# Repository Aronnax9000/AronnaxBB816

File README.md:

# AronnaxBB816
Memory Board
16777216 bytes = 16 MB = 0x1000000
65536 bytes = 64 KB 0x10000 (0x0000 - 0xFFFF)
There are sixteen 64 KB banks in a megabyte.
2^20 1 megabyte 0x100000 

0x000000-0x07FFFF Low  512 KB RAM
0x080000-0x0FFFFF High 512 KB RAM
0x000100-0x0001FF Bank 0 Page 1 I/O
                  VIA 0 (16 bytes)
                  VIA 1 (16 bytes)
                  ACIA (4 bytes)
                  
0x008000-0x00FFFF EEPROM (read when E signal is active)
                  RAM (write always on ~WR, read when E signal is not active)

Board uses A0-A19 (20 lines). 

Active when MEG0 = ~A23 * ~A22 * ~A21 * ~A20.
MEG0_UPPER = MEG0 * A19
MEG0_LOWER = MEG0 * ~A19

~BANK0_UPPER = ~BANK0 + ~A15
~BANK0_LOWER = ~BANK0 + A15

~EEPROM_CS = ~E + ~BANK0_UPPER

I/O Active when BANK0_LOWER * A8 * ~A9 * ~A10 * ~A11 * ~A12 * ~A13 * ~A14

Vector Pull Rewrite

2.28 Vector Pull (VPB)

The Vector Pull active low output indicates that a vector location is being addressed during an interrupt
sequence. VPB is low during the last two interrupt sequence cycles, during which time the processor loads
the PC with the interrupt handler vector location. The VPB signal may be used to select and prioritize
interrupts from several sources by modifying the vector addresses.

Table 5-2 Emulation Mode Vector Locations (8-bit Mode)

|Address | Label | Function | 
00FFFE,F | IRQB/BRK | Hardware/Software | 
00FFFC,D | RESETB | Hardware | 
00FFFA,B | NMIB | Hardware | 
00FFF8,9 | ABORTB | | Hardware | 
00FFF6,7 | (Reserved) | Hardware | 
00FFF4,5 | COP | Software | 
00FFF2,3 | (Reserved) | 
00FFF0,1 | (Reserved) | 

Table 5-3 Native Mode Vector Locations (16-bit Mode)

Address | Label | Function | 
00FFEE,F | IRQB | Hardware | 
00FFEC,D | (Reserved) | 
00FFEA,B | NMIB | Hardware | 
00FFE8,9 | ABORTB| | 
00FFE6,7 | BRK | Software | 
00FFE4,5 | COP | Software| 
00FFE2,3 | (Reserved) | |
00FFE0,1 | (Reserved) | |

The VP output is low during the two cycles used for vector location access. When an interrupt is executed,
D=0 and I=1 in Status Register P.

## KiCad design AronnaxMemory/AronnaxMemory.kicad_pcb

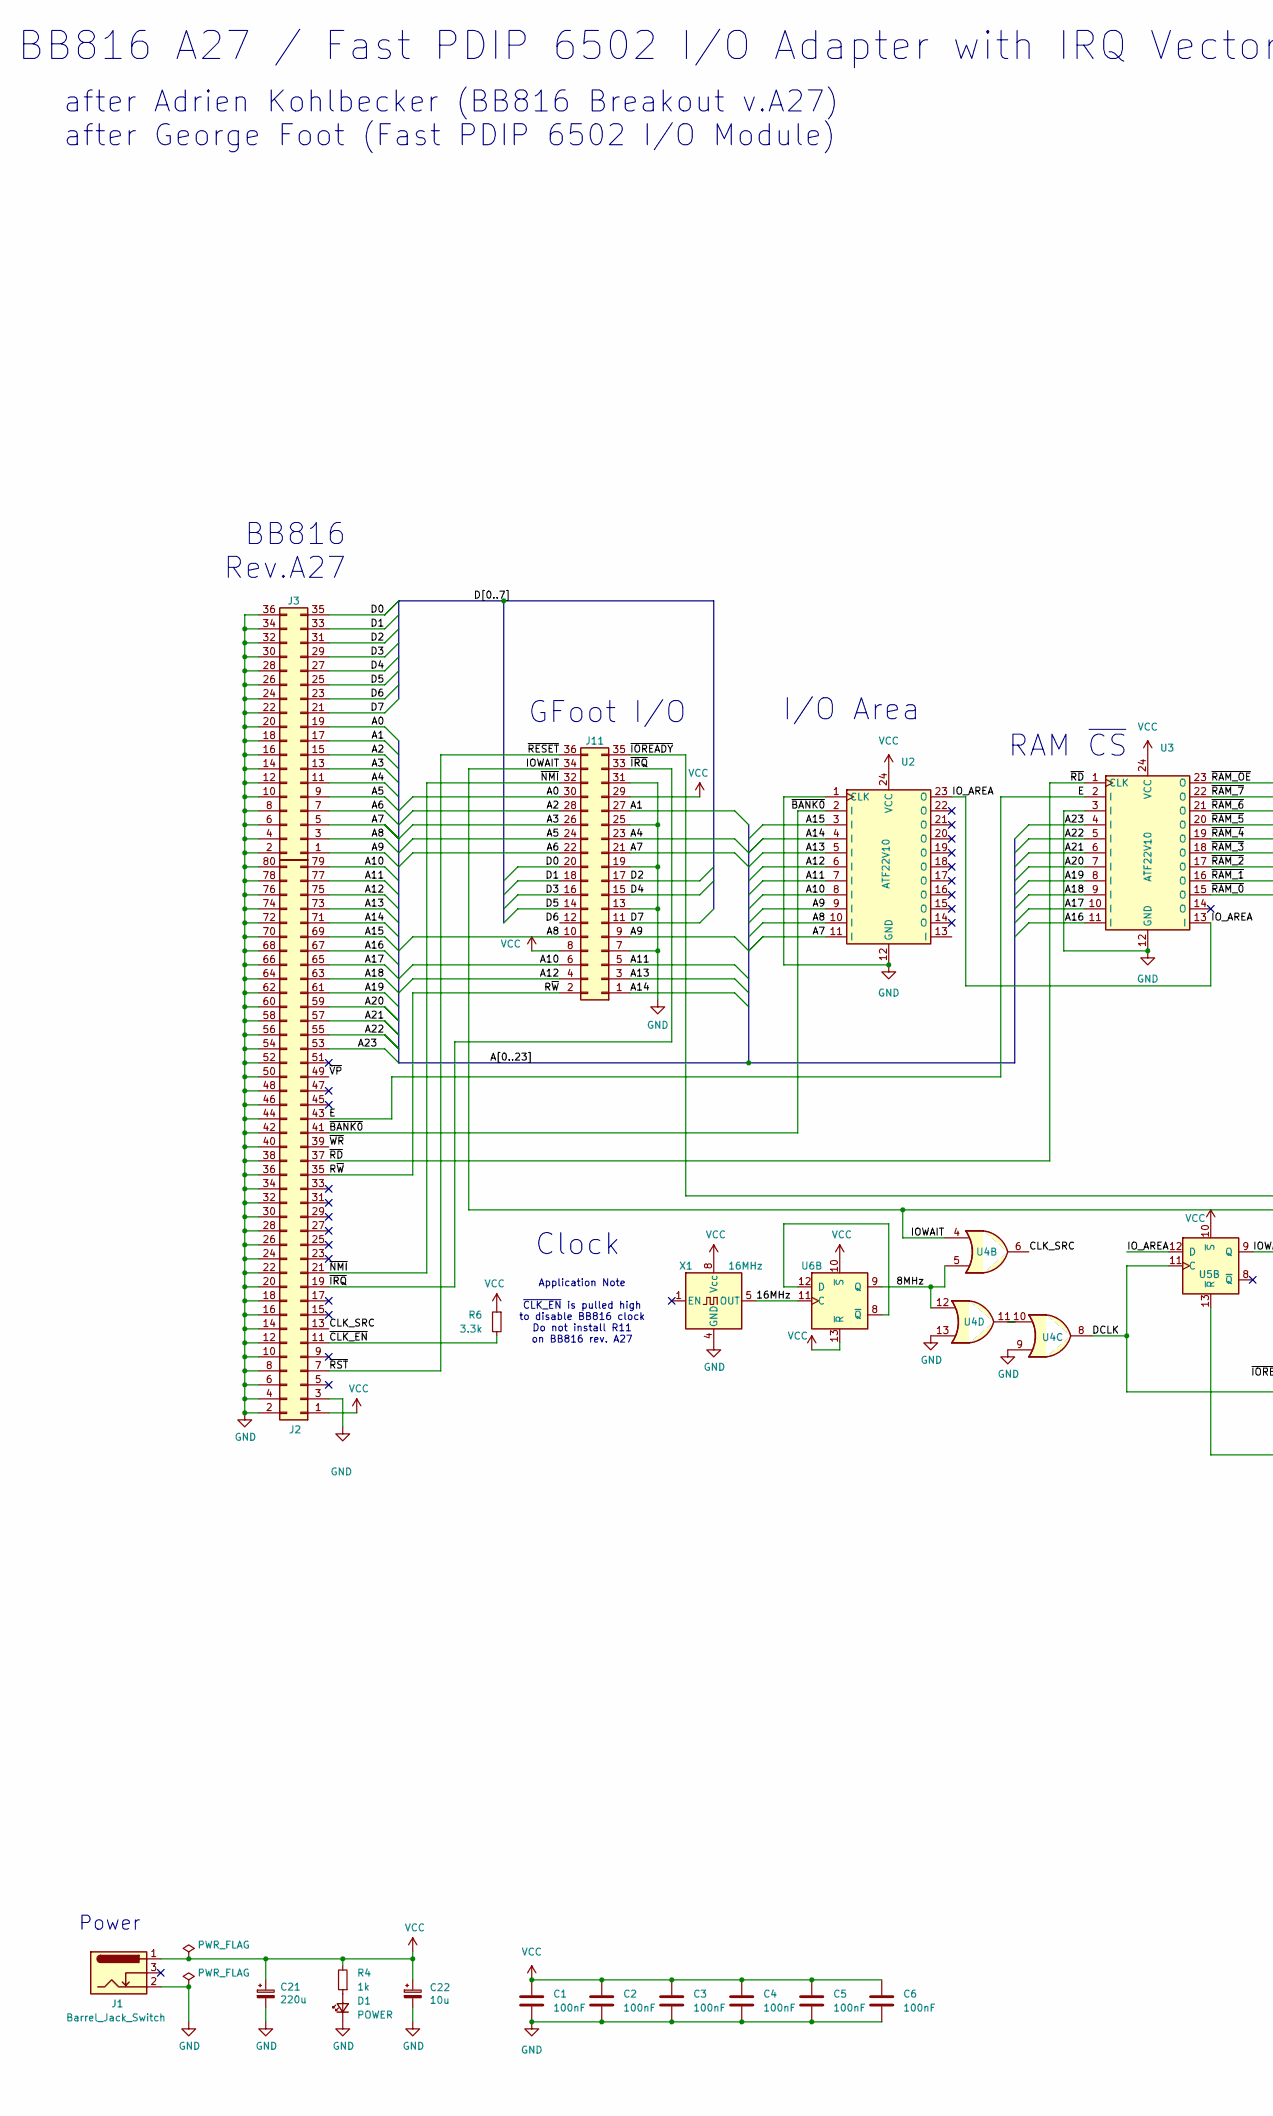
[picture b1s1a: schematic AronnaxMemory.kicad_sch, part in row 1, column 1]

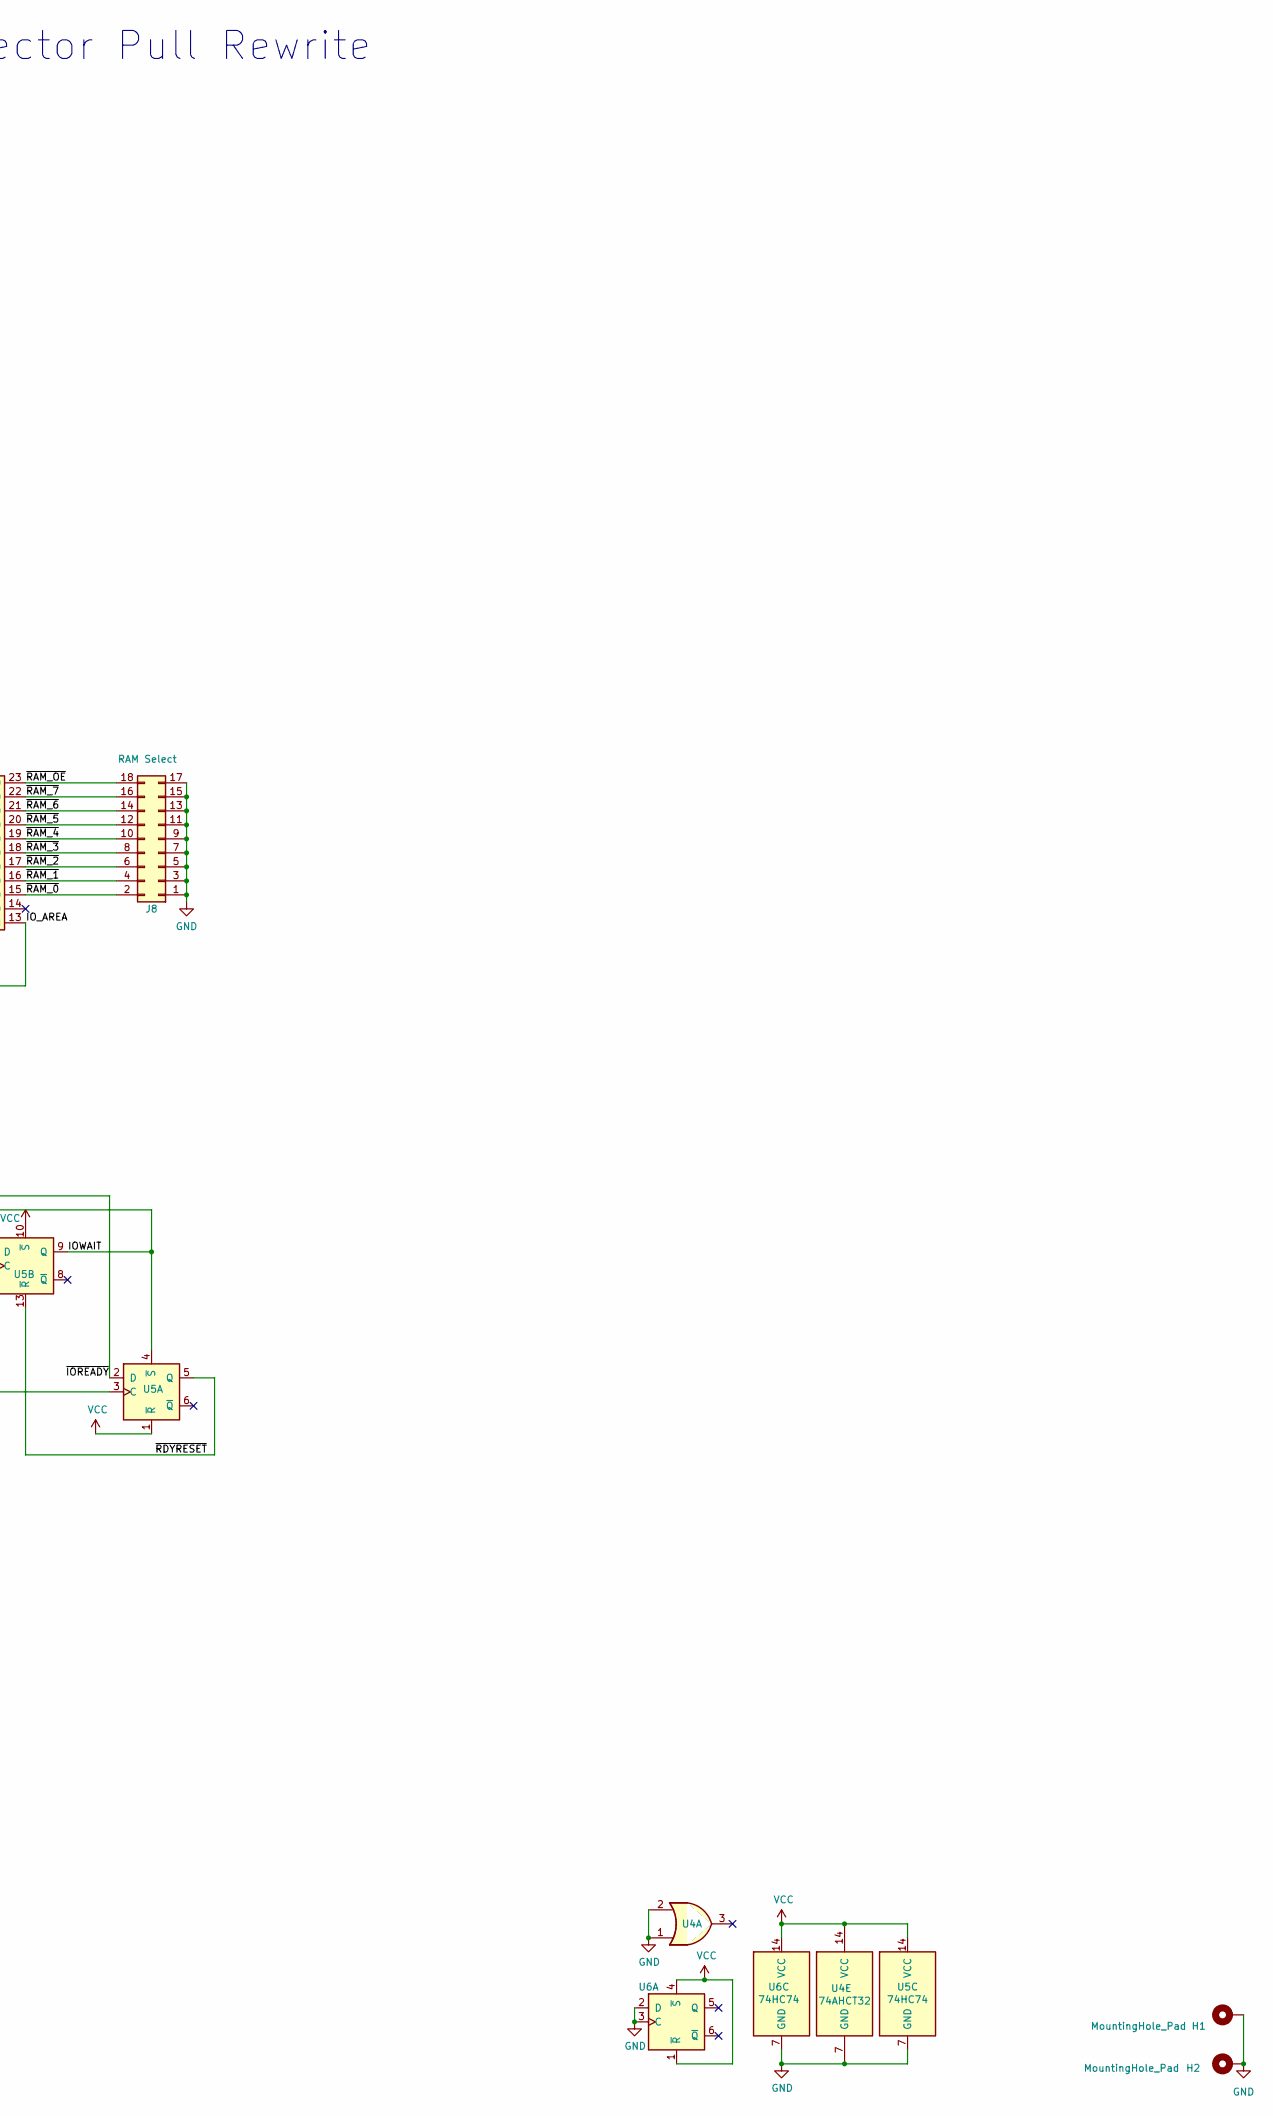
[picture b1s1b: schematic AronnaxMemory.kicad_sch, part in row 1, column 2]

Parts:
C1, C2, C3, C4, C5, C6: 100nF; C_Disc_D3.4mm_W2.1mm_P2.50mm
C21: 220u; CP_Radial_D6.3mm_P2.50mm
C22: 10u; CP_Radial_D4.0mm_P1.50mm
D1: POWER; LED_D3.0mm
H1, H2: MountingHole_Pad; MountingHole_3.2mm_M3_Pad
J1: Barrel_Jack_Switch; BarrelJack_Horizontal
J2: Conn_02x40_Odd_Even; PinHeader_2x40_P2.54mm_Vertical
J3: Conn_02x18_Odd_Even; PinHeader_2x18_P2.54mm_Vertical
J8: RAM Select; PinHeader_2x09_P2.54mm_Vertical
J11: Conn_02x18_Odd_Even; PCB_Edge_36pin
R4: 1k; R_Axial_DIN0207_L6.3mm_D2.5mm_P7.62mm_Horizontal
R6: 3.3k; R_Axial_DIN0207_L6.3mm_D2.5mm_P7.62mm_Horizontal
U2, U3: ATF22V10; DIP-24_W7.62mm_Socket
U4: 74AHCT32; DIP-14_W7.62mm_Socket
U5, U6: 74HC74; DIP-14_W7.62mm_Socket
X1: 16MHz; Oscillator_DIP-8

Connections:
/8MHz: U4.5, U4.12, U6.9 (Q)
/16MHz: U6.11 (C), X1.5 (OUT)
/A0: J3.19, J11.30
/A1: J3.17, J11.27
/A2: J3.15, J11.28
/A3: J3.13, J11.26
/A4: J3.11, J11.23
/A5: J3.9, J11.24
/A6: J3.7, J11.22
/A7: J3.5, J11.21, U2.11 (I)
/A8: J3.3, J11.10, U2.10 (I)
/A9: J3.1, J11.9, U2.9 (I)
/A10: J2.79, J11.6, U2.8 (I)
/A11: J2.77, J11.5, U2.7 (I)
/A12: J2.75, J11.4, U2.6 (I)
/A13: J2.73, J11.3, U2.5 (I)
/A14: J2.71, J11.1, U2.4 (I)
/A15: J2.69, U2.3 (I)
/A16: J2.67, U3.11 (I)
/A17: J2.65, U3.10 (I)
/A18: J2.63, U3.9 (I)
/A19: J2.61, U3.8 (I)
/A20: J2.59, U3.7 (I)
/A21: J2.57, U3.6 (I)
/A22: J2.55, U3.5 (I)
/A23: J2.53, U3.4 (I)
/CLK_SRC: J2.13, U4.6
/D0: J3.35, J11.20
/D1: J3.33, J11.18
/D2: J3.31, J11.17
/D3: J3.29, J11.16
/D4: J3.27, J11.15
/D5: J3.25, J11.14
/D6: J3.23, J11.12
/D7: J3.21, J11.11
/DCLK: U4.8, U5.3 (C), U5.11 (C)
/E: J2.43, U3.2 (I)
/IOWAIT: J11.34, U4.4, U5.4 (~S), U5.9 (Q)
/IO_AREA: U2.23 (O), U3.13 (I), U5.12 (D)
/R~W: J2.35, J11.2
/~BANK0: J2.41, U2.2 (I)
/~CLK_EN: J2.11, R6.2
/~IOREADY: J11.35, U5.2 (D)
/~IRQ: J2.19, J11.33
/~NMI: J2.21, J11.32
/~RAM_0: J8.2, U3.15 (O)
/~RAM_1: J8.4, U3.16 (O)
/~RAM_2: J8.6, U3.17 (O)
/~RAM_3: J8.8, U3.18 (O)
/~RAM_4: J8.10, U3.19 (O)
/~RAM_5: J8.12, U3.20 (O)
/~RAM_6: J8.14, U3.21 (O)
/~RAM_7: J8.16, U3.22 (O)
/~RAM_OE: J8.18, U3.23 (O)
/~RDYRESET: U5.5 (Q), U5.13 (~R)
/~RD: J2.37, U3.1 (CLK)
/~RESET: J2.7, J11.36
/~VP: J2.49
/~WR: J2.39
GND: C1.2, C2.2, C3.2, C4.2, C5.2, C6.2, C21.2, C22.2, D1.1 (K), H1.1, H2.1, J1.2, J2.2, J2.3, J2.4, J2.6, J2.8, J2.10, J2.12, J2.14, J2.16, J2.18, J2.20, J2.22, J2.24, J2.26, J2.28, J2.30, J2.32, J2.34, J2.36, J2.38, J2.40, J2.42, J2.44, J2.46, J2.48, J2.50, J2.52, J2.54, J2.56, J2.58, J2.60, J2.62, J2.64, J2.66, J2.68, J2.70, J2.72, J2.74, J2.76, J2.78, J2.80, J3.2, J3.4, J3.6, J3.8, J3.10, J3.12, J3.14, J3.16, J3.18, J3.20, J3.22, J3.24, J3.26, J3.28, J3.30, J3.32, J3.34, J3.36, J8.1, J8.3, J8.5, J8.7, J8.9, J8.11, J8.13, J8.15, J8.17, J11.7, J11.13, J11.19, J11.25, J11.31, U2.1 (CLK), U2.12 (GND), U3.3 (I), U3.12 (GND), U4.1, U4.2, U4.7 (GND), U4.9, U4.13, U5.7 (GND)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
unnamed: D1.2 (A), R4.1
unnamed: U4.10, U4.11
unnamed: U6.8 (~Q), U6.12 (D)
VCC: C1.1, C2.1, C3.1, C4.1, C5.1, C6.1, C21.1, C22.1, J1.1, J2.1, J11.8, J11.29, R4.2, R6.1, U2.24 (VCC), U3.24 (VCC), U4.14 (VCC), U5.1 (~R), U5.10 (~S), U5.14 (VCC), U6.1 (~R), U6.4 (~S), U6.10 (~S), U6.13 (~R), U6.14 (VCC), X1.8 (Vcc)

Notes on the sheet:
RAM ~{CS}
Power
GFoot I/O
BB816 Rev.A27
after Adrien Kohlbecker (BB816 Breakout v.A27) after George Foot (Fast PDIP 6502 I/O Module)
Clock
I/O Area
BB816 A27 / Fast PDIP 6502 I/O Adapter with IRQ Vector Pull Rewrite
Application Note ~{CLK_EN} is pulled high to disable BB816 clock Do not install R11 on BB816 rev. A27

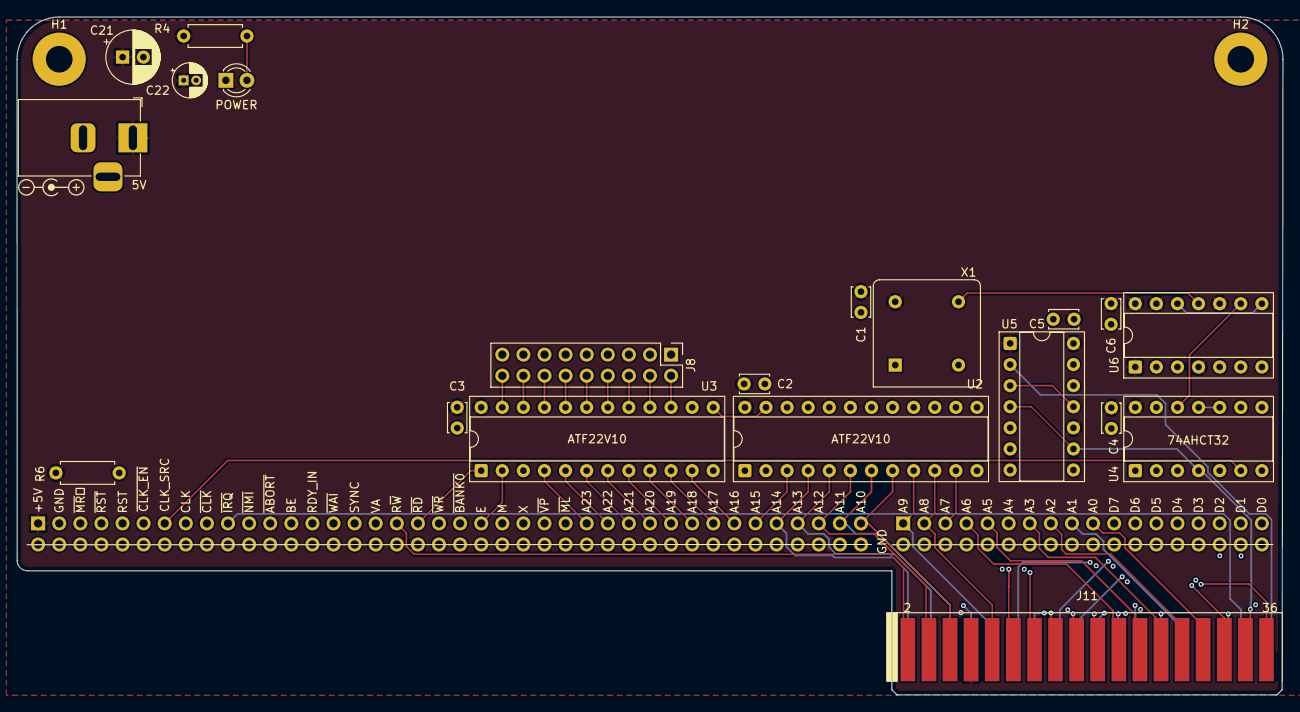
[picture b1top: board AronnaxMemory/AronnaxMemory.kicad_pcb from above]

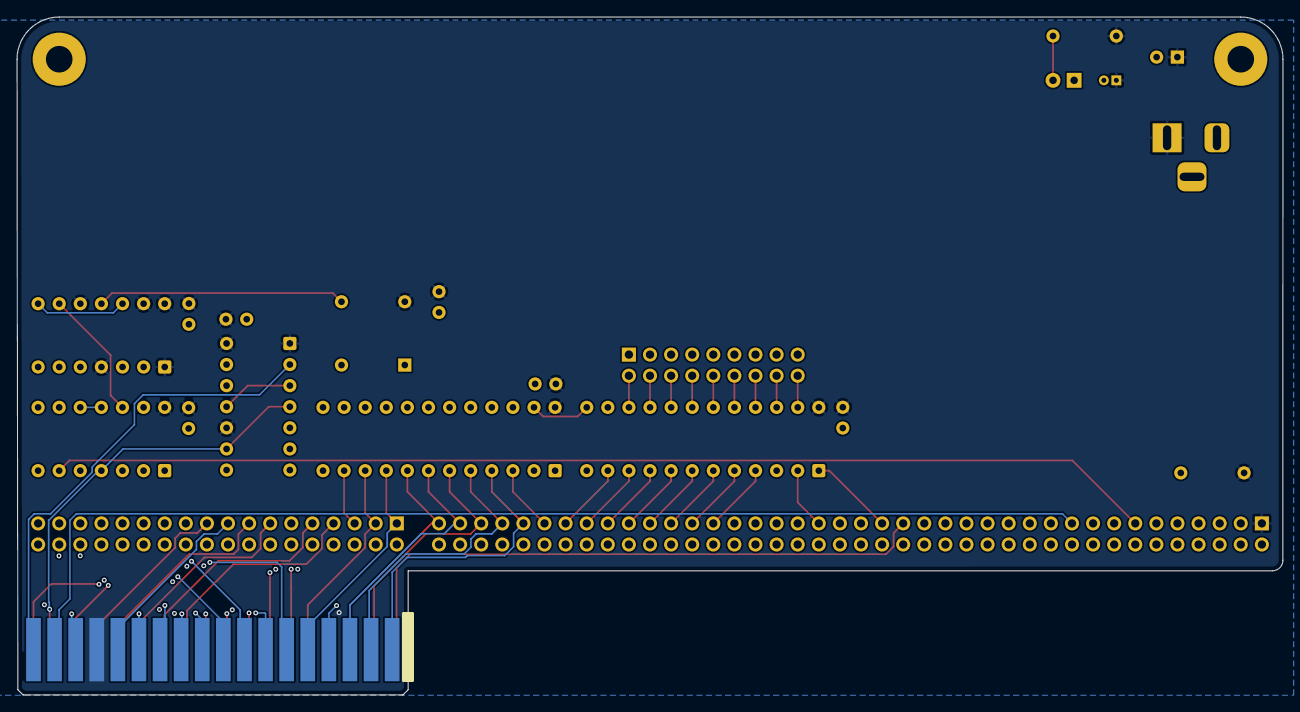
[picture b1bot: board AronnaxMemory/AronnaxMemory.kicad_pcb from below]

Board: 6 copper layers, 152.4 x 81.6 mm, 24 parts (2 on the bottom side), 62 nets.

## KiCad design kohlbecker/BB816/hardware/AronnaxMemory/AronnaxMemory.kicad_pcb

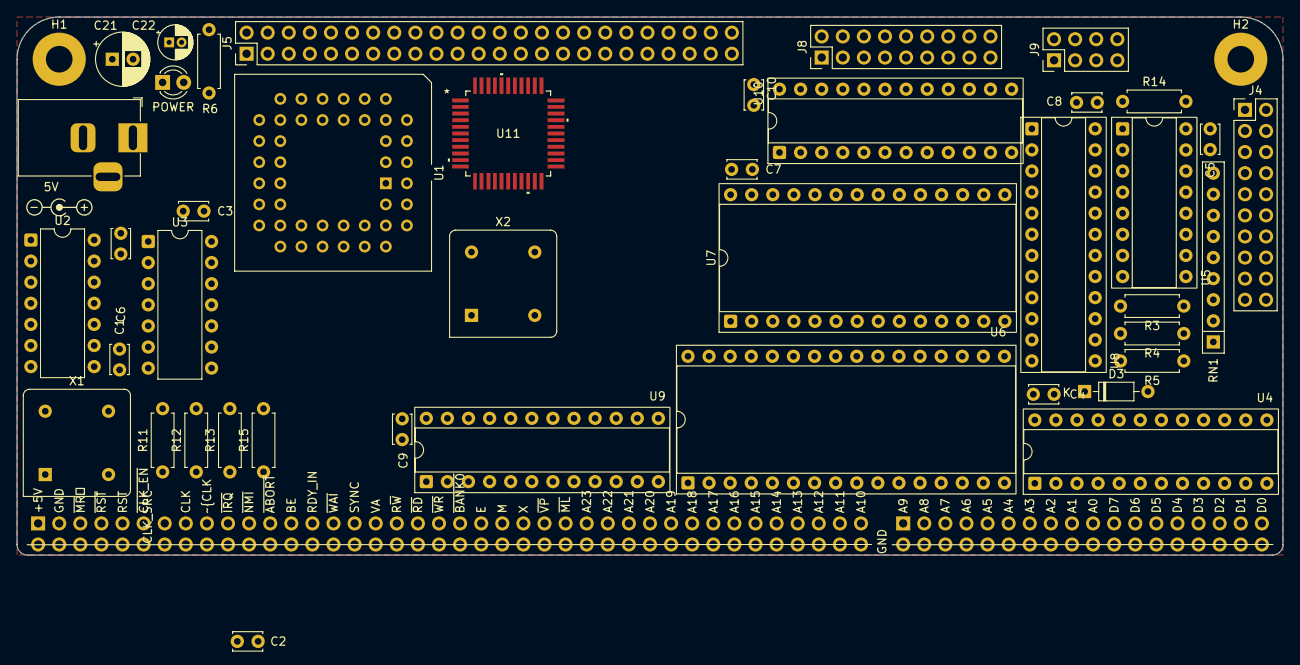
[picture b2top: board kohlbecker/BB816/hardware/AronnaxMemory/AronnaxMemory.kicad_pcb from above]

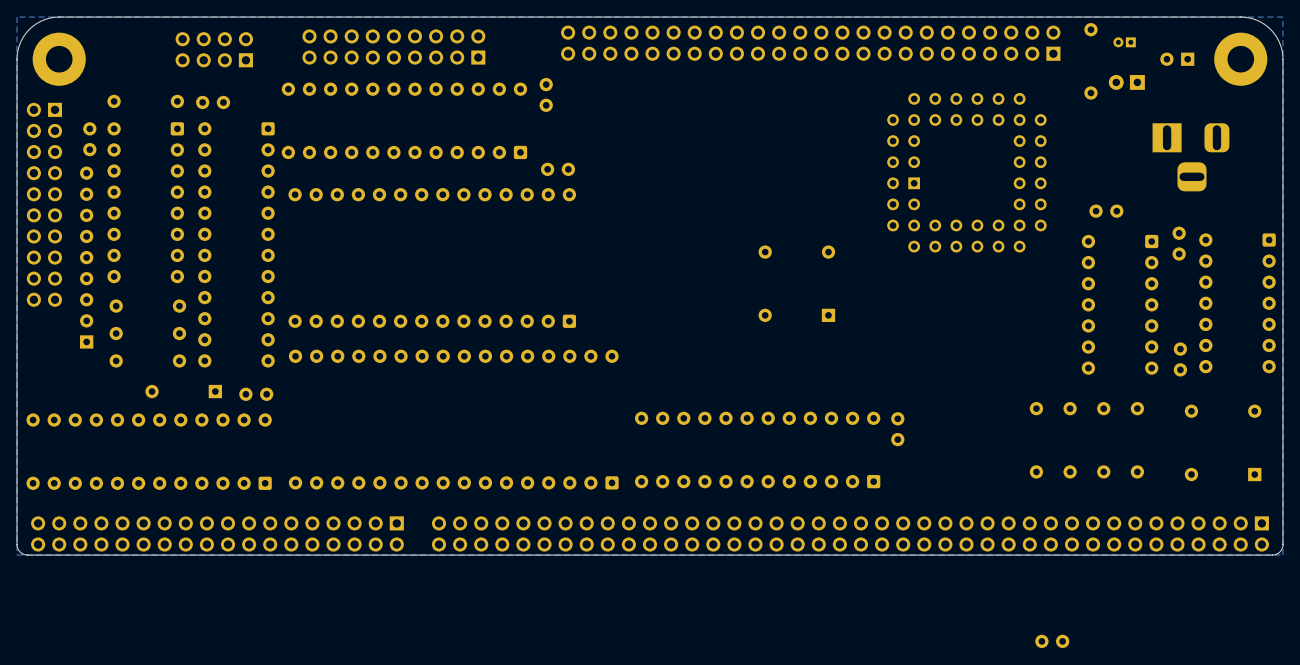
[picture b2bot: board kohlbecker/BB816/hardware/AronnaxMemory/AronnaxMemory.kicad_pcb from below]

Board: 6 copper layers, 152.4 x 64.8 mm, 46 parts (2 on the bottom side), 83 nets, no tracks yet.

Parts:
C1, C2, C3, C4, C5, C6, C7, C8, C9, C10: 100nF; C_Disc_D3.4mm_W2.1mm_P2.50mm
C21: 220u; CP_Radial_D6.3mm_P2.50mm
C22: 10u; CP_Radial_D4.0mm_P1.50mm
D1: POWER; LED_D3.0mm
D3: 1N4148; D_DO-35_SOD27_P7.62mm_Horizontal
H1, H2: MountingHole_Pad; MountingHole_3.2mm_M3_Pad
J1: Barrel_Jack_Switch; BarrelJack_Horizontal
J2: Conn_02x40_Odd_Even; PinHeader_2x40_P2.54mm_Vertical
J3: Conn_02x18_Odd_Even; PinHeader_2x18_P2.54mm_Vertical
J4: I/O; PinHeader_2x10_P2.54mm_Vertical
J5: I/O; PinHeader_2x24_P2.54mm_Vertical
J8: RAM CTL; PinHeader_2x09_P2.54mm_Vertical
J9: IRQ A1-4; PinHeader_2x04_P2.54mm_Vertical
R3, R4, R5, R14: 10K; R_Axial_DIN0207_L6.3mm_D2.5mm_P7.62mm_Horizontal
R6: 1k; R_Axial_DIN0207_L6.3mm_D2.5mm_P7.62mm_Horizontal
R11, R13: 3.3k; R_Axial_DIN0207_L6.3mm_D2.5mm_P7.62mm_Horizontal
R12, R15: 100k; R_Axial_DIN0207_L6.3mm_D2.5mm_P7.62mm_Horizontal
RN1: 100k; R_Array_SIP9
U1: W65C22SxP; PLCC-44_THT-Socket
U2: 74HC74; DIP-14_W7.62mm
U3: 74AHC125; DIP-14_W7.62mm
U4, U8, U9, U10: ATF22V10; DIP-24_W7.62mm_Socket
U5: 74LS348; DIP-16_W7.62mm_Socket
U6: AS6C4008-55PCN; DIP-32_W15.24mm_Socket
U7: AT28C256-15PC; DIP-28_W15.24mm_Socket
U11: TL28L92IFR; FR44
X1, X2: 28MHz; Oscillator_DIP-8

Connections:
/A0: J3.19, U6.12 (A0), U7.10 (A0), U8.11 (I)
/A1: U4.2 (I), U8.10 (I)
/A2: U4.3 (I), U8.9 (I)
/A3: U4.4 (I), U8.8 (I)
/A4: U4.5 (I), U8.7 (I)
/A5: J3.9, U6.7 (A5), U7.5 (A5), U8.6 (I)
/A6: J3.7, U6.6 (A6), U7.4 (A6), U8.5 (I)
/A7: J3.5, U6.5 (A7), U7.3 (A7), U8.4 (I)
/A8: J3.3, U6.27 (A8), U7.25 (A8), U8.3 (I), U9.10 (I)
/A9: J3.1, U6.26 (A9), U7.24 (A9), U8.2 (I), U9.9 (I)
/A10: J2.79, U6.23 (A10), U7.21 (A10), U8.1 (CLK), U9.8 (I)
/A11: J2.77, U6.25 (A11), U7.23 (A11), U9.7 (I)
/A12: J2.75, U6.4 (A12), U7.2 (A12), U9.6 (I)
/A13: J2.73, U6.28 (A13), U7.26 (A13), U9.5 (I)
/A14: J2.71, U6.3 (A14), U7.1 (A14), U9.4 (I)
/A15: J2.69, U6.31 (A15), U9.3 (I)
/A16: J2.67, U6.2 (A16), U10.9 (I)
/A17: J2.65, U6.30 (A17), U10.8 (I)
/A18: J2.63, U6.1 (A18), U10.7 (I)
/A19: J2.61, U10.6 (I)
/A20: J2.59, U10.5 (I)
/A21: J2.57, U10.4 (I)
/A22: J2.55, U10.3 (I)
/A23: J2.53, U10.2 (I)
/AA1: J3.17, J9.7, U4.17 (O), U6.11 (A1), U7.9 (A1)
/AA2: J3.15, J9.5, U4.18 (O), U6.10 (A2), U7.8 (A2)
/AA3: J3.13, J9.3, U4.19 (O), U6.9 (A3), U7.7 (A3)
/AA4: J3.11, J9.1, U4.20 (O), U6.8 (A4), U7.6 (A4)
/ADDEND_AA1: R5.2, U4.7 (I), U5.9 (A0)
/ADDEND_AA2: R4.2, U4.8 (I), U5.7 (A1)
/ADDEND_AA3: R3.2, U4.9 (I), U5.6 (A2)
/D0: J3.35, U6.13 (DQ0), U7.11 (D0)
/D1: J3.33, U6.14 (DQ1), U7.12 (D1)
/D2: J3.31, U6.15 (DQ2), U7.13 (D2)
/D3: J3.29, U6.17 (DQ3), U7.15 (D3)
/D4: J3.27, U6.18 (DQ4), U7.16 (D4)
/D5: J3.25, U6.19 (DQ5), U7.17 (D5)
/D6: J3.23, U6.20 (DQ6), U7.18 (D6)
/D7: J3.21, U6.21 (DQ7), U7.19 (D7)
/TurboClock/7MHz: U2.5 (Q), U3.2
/TurboClock/14MHz: U2.3 (C), U2.9 (Q), U3.9
/TurboClock/28MHz: U2.11 (C), X1.5 (OUT)
/TurboClock/CLK_SRC: R12.1, R15.1, U3.3, U3.8
/TurboClock/E: R11.1, U3.10
/TurboClock/~E: R13.1, U3.1
/~NMI: J2.21, U4.21 (O)
/~VP: J2.49, U4.10 (I)
E: J2.43, U9.11 (I)
GND: C1.2, C2.2, C3.2, C4.2, C5.2, C6.2, C7.2, C8.2, C9.2, C10.2, C21.2, C22.2, D1.1 (K), H1.1, H2.1, J1.2, J2.2, J2.3, J2.4, J2.6, J2.8, J2.10, J2.12, J2.14, J2.16, J2.18, J2.20, J2.22, J2.24, J2.26, J2.28, J2.30, J2.32, J2.34, J2.36, J2.38, J2.40, J2.42, J2.44, J2.46, J2.48, J2.50, J2.52, J2.54, J2.56, J2.58, J2.60, J2.62, J2.64, J2.66, J2.68, J2.70, J2.72, J2.74, J2.76, J2.78, J2.80, J3.2, J3.4, J3.6, J3.8, J3.10, J3.12, J3.14, J3.16, J3.18, J3.20, J3.22, J3.24, J3.26, J3.28, J3.30, J3.32, J3.34, J3.36, J4.4, J4.8, J4.12, J4.16, J4.20, J8.2, J8.4, J8.6, J8.8, J8.10, J8.12, J8.14, J8.16, J8.18, J9.2, J9.4, J9.6, J9.8, R3.1, R4.1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
unnamed: D1.2 (A), R6.1
unnamed: D3.1 (K), R14.2, U5.14 (GS)
unnamed: U2.2 (D), U2.6 (~Q)
unnamed: U2.8 (~Q), U2.12 (D)
VCC: C1.1, C2.1, C3.1, C4.1, C5.1, C6.1, C7.1, C8.1, C9.1, C10.1, C21.1, C22.1, J1.1, J2.1, J4.2, J4.6, J4.10, J4.14, J4.18, R6.2, R13.2, R14.1, RN1.1 (common), U2.1 (~R), U2.4 (~S), U2.10 (~S), U2.13 (~R), U2.14 (VCC), U3.14 (VCC), U4.24 (VCC), U5.15 (E0), U5.16 (VCC), U6.32 (VCC), U7.28 (VCC), U8.24 (VCC), U9.24 (VCC), U10.24 (VCC), X1.8 (Vcc)
~BANK0: J2.41, U9.2 (I)
~CLK_EN: J2.11, U9.20 (O)
~IO_3: J4.1, U8.20 (O)
~IO_4: J4.5, U8.19 (O)
~IO_5: J4.9, U8.18 (O)
~IO_6: J4.13, U8.17 (O)
~IO_7: J4.17, U8.16 (O)
~IRQ0: RN1.9 (R8), U5.1 (4)
~IRQ1: RN1.8 (R7), U5.2 (5)
~IRQ2: RN1.7 (R6), U5.3 (6)
~IRQ3: J4.3, RN1.6 (R5), U5.4 (7)
~IRQ4: J4.7, RN1.5 (R4), U5.13 (3)
~IRQ5: J4.11, RN1.4 (R3), U5.12 (2)
~IRQ6: J4.15, RN1.3 (R2), U5.11 (1)
~IRQ7: J4.19, RN1.2 (R1), U5.10 (0)
~IRQ: D3.2 (A), J2.19, U4.16 (O)
~I/O: U8.13 (I), U9.23 (O), U10.10 (I)
~MEG0: J8.15, U10.15 (O)
~MEG2: J8.13, U10.16 (O)
~MEG4: J8.11, U10.17 (O)
~MEG6: J8.9, U10.18 (O)
~MEG8: J8.7, U10.19 (O)
~MEGA: J8.5, U10.20 (O)
~MEGC: J8.3, U10.21 (O)
~MEGE: J8.1, U10.22 (O)
~RAM_OE: J8.17, U9.21 (O)
~RD: J2.37, U10.1 (CLK)
~ROM_OE: U7.22 (~OE), U9.22 (O), U10.11 (I)
~WR: J2.39, U7.27 (~WE)

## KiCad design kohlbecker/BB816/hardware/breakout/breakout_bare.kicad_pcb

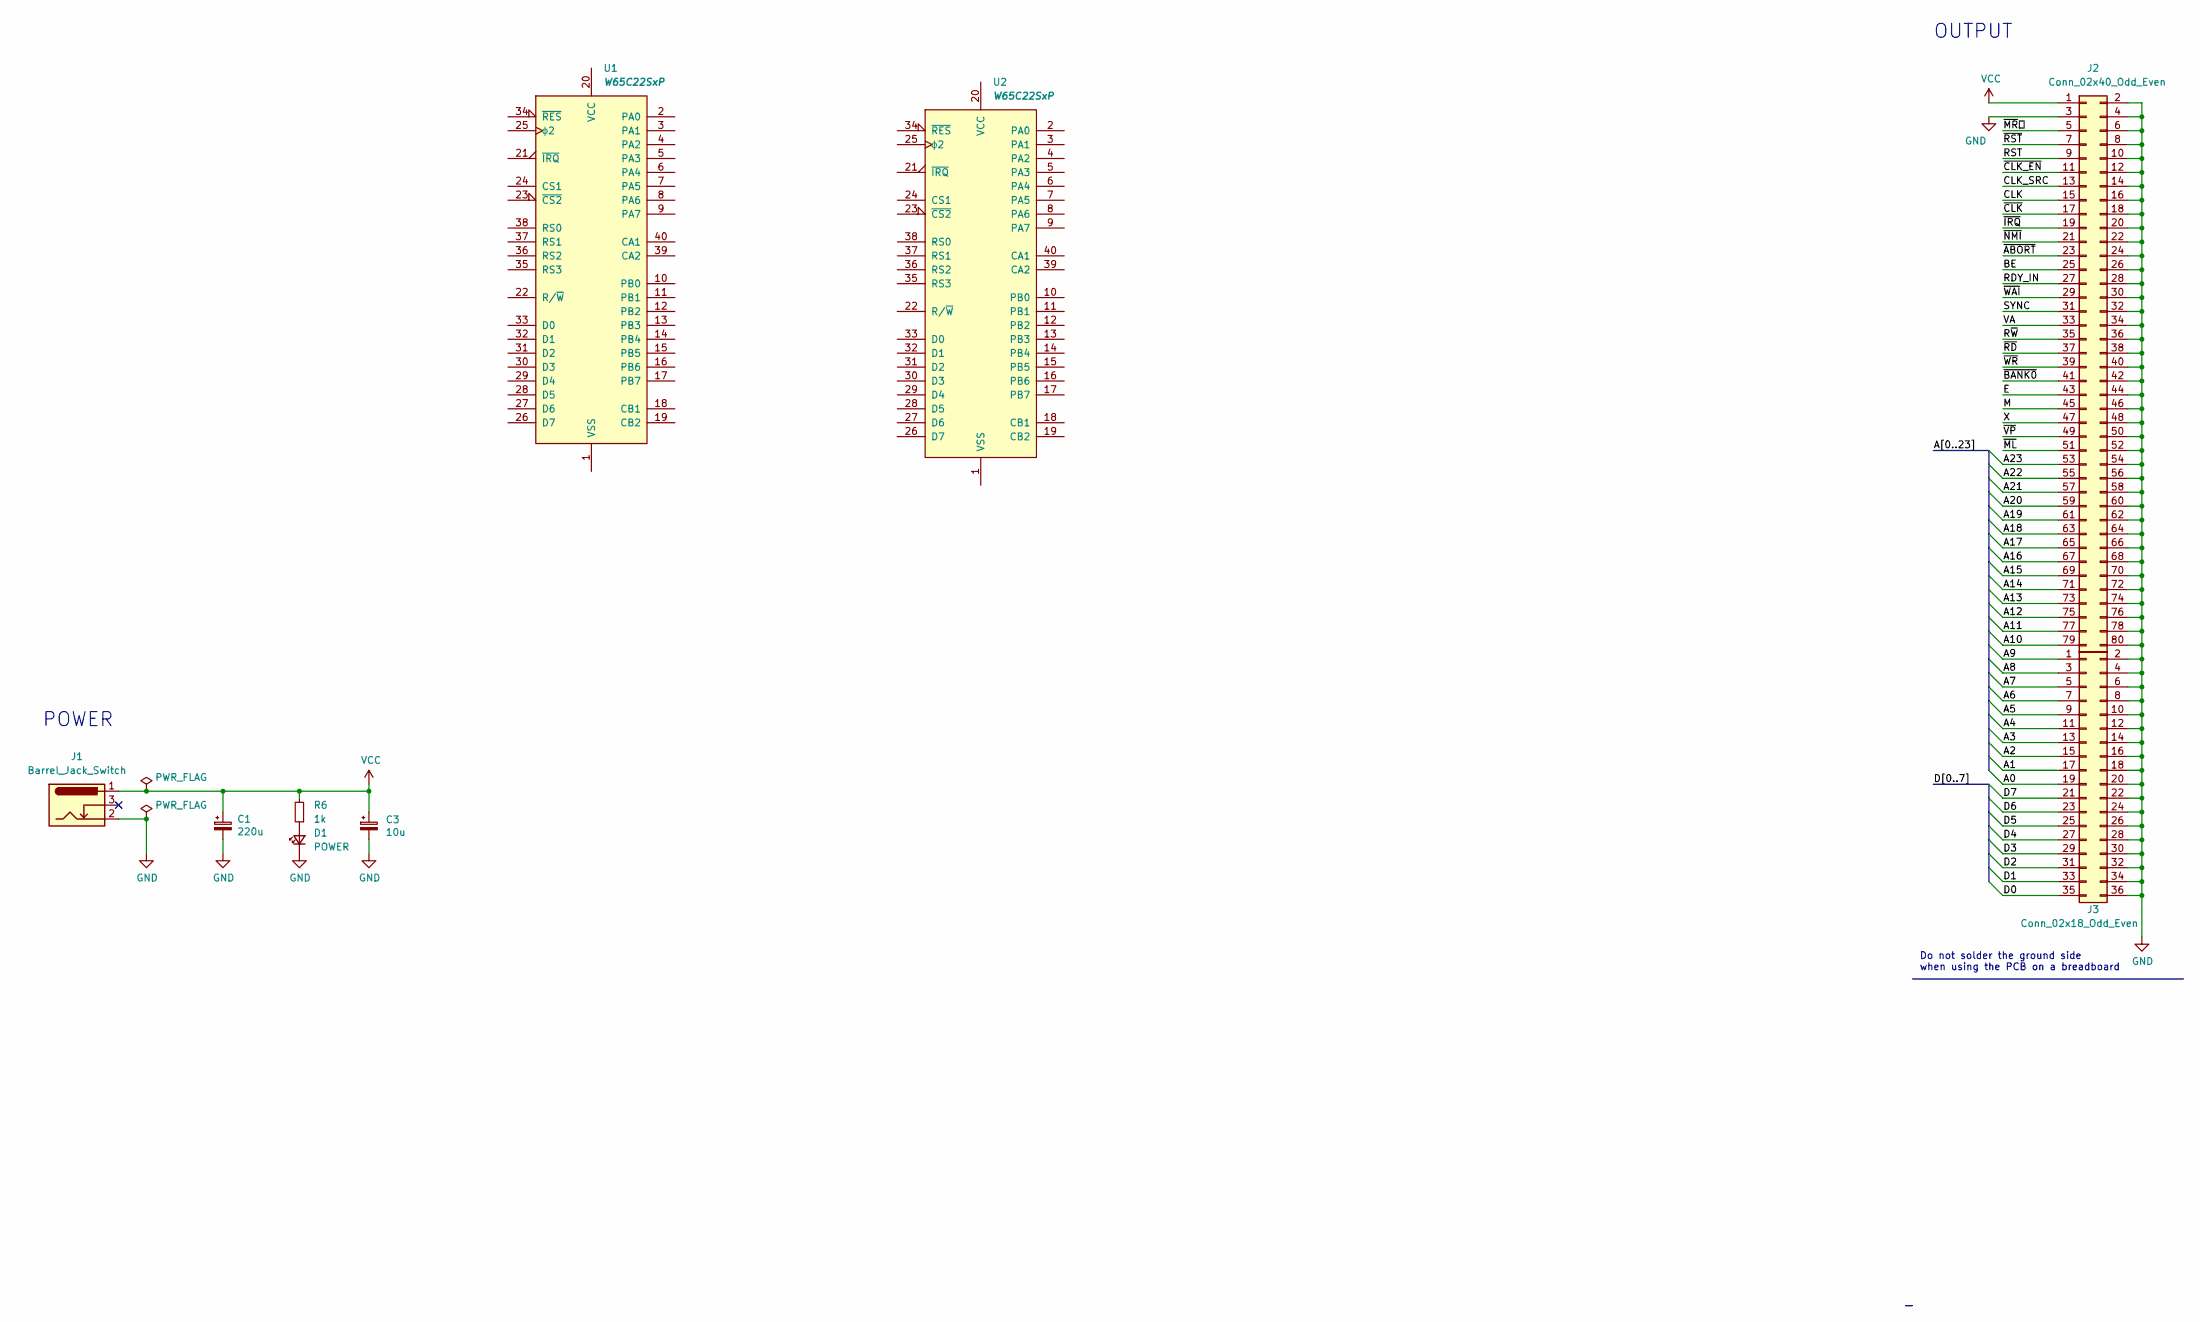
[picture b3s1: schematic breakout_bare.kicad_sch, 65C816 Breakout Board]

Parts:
C1: 220u; CP_Radial_D6.3mm_P2.50mm
C3: 10u; CP_Radial_D4.0mm_P1.50mm
D1: POWER; LED_D3.0mm
J1: Barrel_Jack_Switch; BarrelJack_Horizontal
J2: Conn_02x40_Odd_Even; PinHeader_2x40_P2.54mm_Vertical
J3: Conn_02x18_Odd_Even; PinHeader_2x18_P2.54mm_Vertical
R6: 1k; R_Axial_DIN0207_L6.3mm_D2.5mm_P7.62mm_Horizontal
U1, U2: W65C22SxP; DIP-40_W15.24mm_Socket

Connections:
/A0: J3.19
/A1: J3.17
/A2: J3.15
/A3: J3.13
/A4: J3.11
/A5: J3.9
/A6: J3.7
/A7: J3.5
/A8: J3.3
/A9: J3.1
/A10: J2.79
/A11: J2.77
/A12: J2.75
/A13: J2.73
/A14: J2.71
/A15: J2.69
/A16: J2.67
/A17: J2.65
/A18: J2.63
/A19: J2.61
/A20: J2.59
/A21: J2.57
/A22: J2.55
/A23: J2.53
/BE: J2.25
/CLK: J2.15
/CLK_SRC: J2.13
/D0: J3.35
/D1: J3.33
/D2: J3.31
/D3: J3.29
/D4: J3.27
/D5: J3.25
/D6: J3.23
/D7: J3.21
/E: J2.43
/M: J2.45
/RDY_IN: J2.27
/RST: J2.9
/R~W: J2.35
/SYNC: J2.31
/VA: J2.33
/X: J2.47
/~ABORT: J2.23
/~BANK0: J2.41
/~CLK_EN: J2.11
/~CLK: J2.17
/~IRQ: J2.19
/~ML: J2.51
/~MR⎒: J2.5
/~NMI: J2.21
/~RD: J2.37
/~RST: J2.7
/~VP: J2.49
/~WAI: J2.29
/~WR: J2.39
GND: C1.2, C3.2, D1.1 (K), J1.2, J2.2, J2.3, J2.4, J2.6, J2.8, J2.10, J2.12, J2.14, J2.16, J2.18, J2.20, J2.22, J2.24, J2.26, J2.28, J2.30, J2.32, J2.34, J2.36, J2.38, J2.40, J2.42, J2.44, J2.46, J2.48, J2.50, J2.52, J2.54, J2.56, J2.58, J2.60, J2.62, J2.64, J2.66, J2.68, J2.70, J2.72, J2.74, J2.76, J2.78, J2.80, J3.2, J3.4, J3.6, J3.8, J3.10, J3.12, J3.14, J3.16, J3.18, J3.20, J3.22, J3.24, J3.26, J3.28, J3.30, J3.32, J3.34, J3.36
unnamed: D1.2 (A), R6.1
VCC: C1.1, C3.1, J1.1, J2.1, R6.2

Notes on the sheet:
Do not solder the ground side when using the PCB on a breadboard
POWER
OUTPUT

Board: 4 copper layers, 9 parts (2 on the bottom side), 3 nets, no tracks yet.

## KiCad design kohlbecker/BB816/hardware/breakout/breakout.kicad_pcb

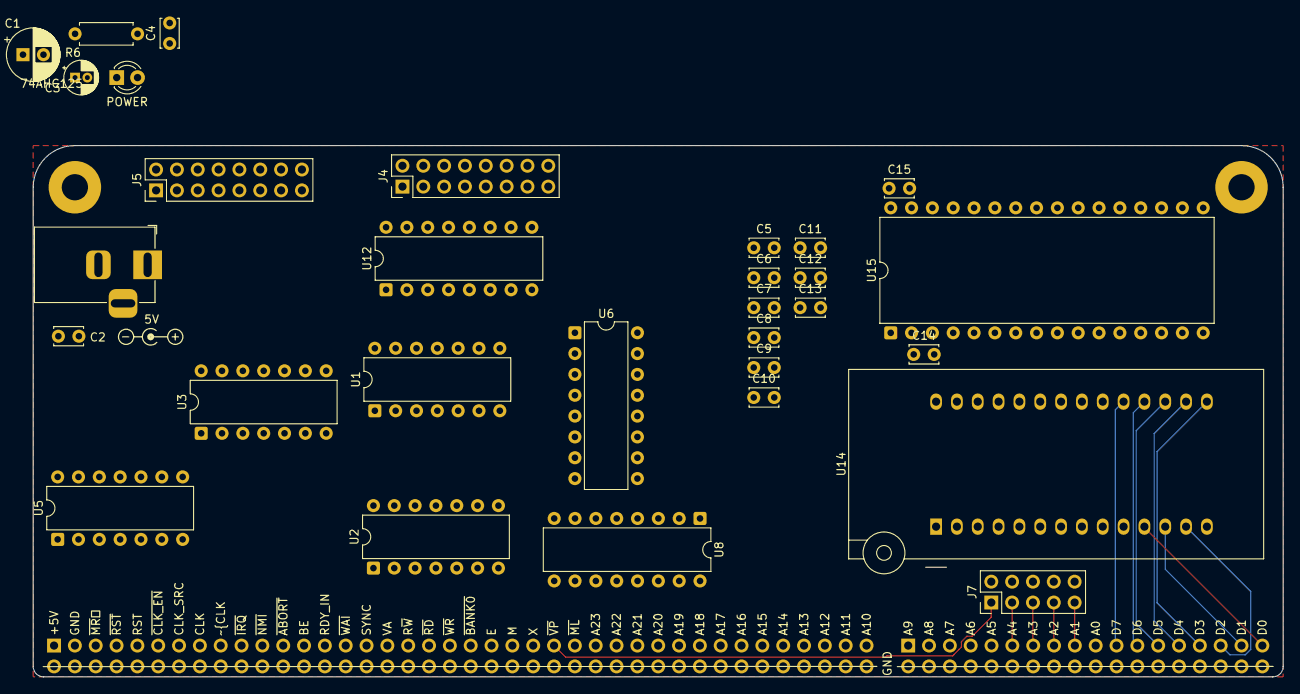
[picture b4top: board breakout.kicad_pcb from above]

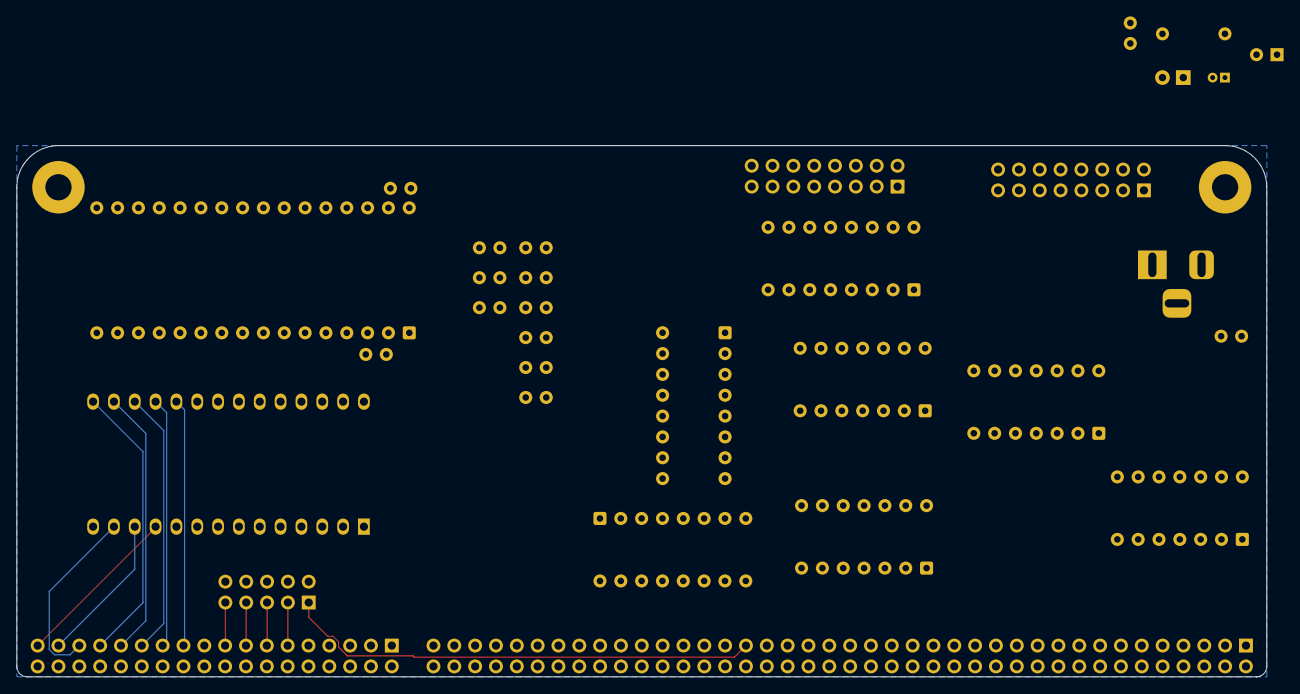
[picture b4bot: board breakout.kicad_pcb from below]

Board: 4 copper layers, 152.4 x 64.8 mm, 34 parts (2 on the bottom side), 68 nets.

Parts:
C1: 220u; CP_Radial_D6.3mm_P2.50mm
C2, C4: 100n; C_Disc_D3.4mm_W2.1mm_P2.50mm
C3: 10u; CP_Radial_D4.0mm_P1.50mm
C5, C6, C7, C8, C9, C10, C11, C12, C13, C14, C15: 100nF; C_Disc_D3.4mm_W2.1mm_P2.50mm
D1: POWER; LED_D3.0mm
H1, H2: MountingHole_Pad; MountingHole_3.2mm_M3_Pad
J1: Barrel_Jack_Switch; BarrelJack_Horizontal
J2: Conn_02x40_Odd_Even; PinHeader_2x40_P2.54mm_Vertical
J3: Conn_02x18_Odd_Even; PinHeader_2x18_P2.54mm_Vertical
J4: I/O; PinHeader_2x08_P2.54mm_Vertical
J5: Decoder Output; PinHeader_2x08_P2.54mm_Vertical
J7: VP_REWR; PinHeader_2x05_P2.54mm_Vertical
R6: 1k; R_Axial_DIN0207_L6.3mm_D2.5mm_P7.62mm_Horizontal
U1: 74LS04; DIP-14_W7.62mm
U2, U3: 74LS32; DIP-14_W7.62mm
U5: 74LS08; DIP-14_W7.62mm
U6, U8, U12: 74LS138; DIP-16_W7.62mm
U14: AT28C256-15PC; DIP_Socket-28_W11.9_W12.7_W15.24_W17.78_W18.5_3M_228-1277-0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
U15: AS6C4008-55PCN; DIP-32_W15.24mm

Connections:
/A0: J3.19, U14.10 (A0), U15.12 (A0)
/A1: J7.10, U14.9 (A1), U15.11 (A1)
/A2: J7.8, U14.8 (A2), U15.10 (A2)
/A3: J7.6, U14.7 (A3), U15.9 (A3)
/A4: J7.4, U14.6 (A4), U15.8 (A4)
/A5: J3.9, U12.1 (A0), U14.5 (A5), U15.7 (A5)
/A6: J3.7, U12.2 (A1), U14.4 (A6), U15.6 (A6)
/A7: J3.5, U12.3 (A2), U14.3 (A7), U15.5 (A7)
/A8: J3.3, U8.1 (A0), U14.25 (A8), U15.27 (A8)
/A9: J3.1, U8.2 (A1), U14.24 (A9), U15.26 (A9)
/A10: J2.79, U8.3 (A2), U14.21 (A10), U15.23 (A10)
/A11: J2.77, U6.1 (A0), U8.5 (E2), U14.23 (A11), U15.25 (A11)
/A12: J2.75, U6.2 (A1), U14.2 (A12), U15.4 (A12)
/A13: J2.73, U6.3 (A2), U14.26 (A13), U15.28 (A13)
/A14: J2.71, U6.5 (E2), U14.1 (A14), U15.3 (A14)
/A15: J2.69, U1.5, U3.10, U15.31 (A15)
/A16: J2.67, U15.2 (A16)
/A17: J2.65, U15.30 (A17)
/A18: J2.63, U15.1 (A18)
/A19: J2.61, U2.13, U5.2
/A20: J2.59, U2.5
/A21: J2.57, U2.4
/A22: J2.55, U2.2
/A23: J2.53, U2.1
/AA1: J3.17, J7.9
/AA2: J3.15, J7.7
/AA3: J3.13, J7.5
/AA4: J3.11, J7.3
/D0: J3.35, U14.11 (D0), U15.13 (DQ0)
/D1: J3.33, U14.12 (D1), U15.14 (DQ1)
/D2: J3.31, U14.13 (D2), U15.15 (DQ2)
/D3: J3.29, U14.15 (D3), U15.17 (DQ3)
/D4: J3.27, U14.16 (D4), U15.18 (DQ4)
/D5: J3.25, U14.17 (D5), U15.19 (DQ5)
/D6: J3.23, U14.18 (D6), U15.20 (DQ6)
/D7: J3.21, U14.19 (D7), U15.21 (DQ7)
/E: J2.43, U1.3, U5.5
/MEG0: U1.2, U5.1
/MEG0_HI: J5.5, U5.3
/~0x00: J4.1, U12.15 (O0)
/~0x20: J4.3, U12.14 (O1)
/~0x60: J4.7, U12.12 (O3)
/~0x80: J4.9, U12.11 (O4)
/~0xA0: J4.11, U12.10 (O5)
/~0xCO: J4.13, U12.9 (O6)
/~0xE0: J4.15, U12.7 (O7)
/~BANK0: J2.41, U3.5, U3.9
/~MEG0: J5.1, U1.1, U2.8, U2.12
/~VP: J2.49, J7.1
/~WR: J2.39, U14.27 (~WE), U15.29 (WE#)
GND: C1.2, C2.2, C3.2, C4.2, C5.2, C6.2, C7.2, C8.2, C9.2, C10.2, C11.2, C12.2, C13.2, C14.2, C15.2, D1.1 (K), H1.1, H2.1, J1.2, J2.2, J2.3, J2.4, J2.6, J2.8, J2.10, J2.12, J2.14, J2.16, J2.18, J2.20, J2.22, J2.24, J2.26, J2.28, J2.30, J2.32, J2.34, J2.36, J2.38, J2.40, J2.42, J2.44, J2.46, J2.48, J2.50, J2.52, J2.54, J2.56, J2.58, J2.60, J2.62, J2.64, J2.66, J2.68, J2.70, J2.72, J2.74, J2.76, J2.78, J2.80, J3.2, J3.4, J3.6, J3.8, J3.10, J3.12, J3.14, J3.16, J3.18, J3.20, J3.22, J3.24, J3.26, J3.28, J3.30, J3.32, J3.34, J3.36, J4.2, J4.4, J4.6, J4.8, J4.10, J4.12, J4.14, J4.16, J5.2, J5.4, J5.6, J5.8, J5.10, J5.12, J5.14, J5.15, J5.16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
unnamed: D1.2 (A), R6.1
unnamed: U1.4, U3.1
unnamed: U1.6, U3.4
unnamed: U1.8, U5.4
unnamed: U1.10, U3.13
unnamed: U2.3, U2.9
unnamed: U2.6, U2.10
unnamed: U3.12, U5.6
unnamed: U5.9, U5.10, U5.12, U5.13
unnamed: U6.15 (O0), U8.4 (E1)
unnamed: U3.11, U15.24 (OE#)
VCC: C1.1, C2.1, C3.1, C4.1, C5.1, C6.1, C7.1, C8.1, C9.1, C10.1, C11.1, C12.1, C13.1, C14.1, C15.1, J1.1, J2.1, R6.2, U1.14 (VCC), U2.14 (VCC), U3.14 (VCC), U5.14 (VCC), U6.6 (E3), U6.16 (VCC), U8.6 (E3), U8.16 (VCC), U12.6 (E3), U12.16 (VCC), U14.28 (VCC), U15.32 (VCC)
~BANK0_HI: J5.7, U1.9, U3.2, U3.6, U14.20 (~CS)
~BANK0_LO: J5.9, U3.8, U6.4 (E1)
~MEG0_LO: J5.3, U2.11, U15.22 (CE#)
~PAGE1: J5.13, U1.11, U8.14 (O1), U12.5 (E2)
~ROM_OE: J5.11, U3.3, U14.22 (~OE)

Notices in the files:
AronnaxMemory/AronnaxMemory.kicad_pcb:
Licensed under CERN-OHL-W v2
Copyright © 2022 Adrien Kohlbecker
